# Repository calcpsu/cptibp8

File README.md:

# CalcPack TI BP8

A Li-Po battery replacement design for TI BP7/8/9 battery pack calculators - e.g. TI-55, TI-30, TI Programmer, etc. The original batteries had ~ 500mAh capacity (@2.4V: 1.2Wh), while a typical 9V alkaline battery substitution as ~500mAh (@9V: 4.5Wh), albeit single-use only.

Li-Po has the advantage of far reduced self-discharge in comparison to Ni-Cd, which is an advantage for an intermittently-used device. Even with similar mAh capacity, we can expect longer battery life.

Ni-CD batteries are notorious for leaking. While Lithium Ion batteries are notorious for self-immolation, a well protected Li-Po battery (particularly in a low current application like this) should be able to be made very safe.

## Features / design goals:
- Direct replacement for a BP8 battery pack, compatible with TI55, TI30, TI Programmer (and other Majestic series).
    - Support both 9V battery snap terminal and 3-pin molex connector output
- Compatible with existing charging connection (2-pin AC input; somewhere from 5 to 9VAC)
    - Provides adequate smoothing of rectified AC
    - Provides voltage clamping / overvoltage protection
- Efficient conversion of input rectified supply to 5VDC for charging IC and calculator operation
- Step up from battery or input rectified supply to 9VDC for calculator supply
- Protected from:
    - Overvoltage (input) at 2x rated voltage and current (IATA requirement)
    - Overcharging (4.2V)
    - Over-discharge (3.1V shutdown, 2.5V cutoff in battery pack)
    - Short circuit and overcurrent (again for IATA requirement)
- Minimum idle/quiescent current to maximise charge time
- Similar or higher capacity than typical Ni-MH altenative (1500mAh @ 2.4V: 3.6Wh)

## Case ##

The board is designed to fit into the original TI case bottom part, to preserve an original look!

1. The simplest installation is to place the board and 3D printed standoff into the original case bottom, with a dab of hot glue to hold it in place.
    * The original back cover will not fit, due to ridges for cylindrical cells - you can leave it off.
    * If you prefer, a 3d-printed replacement top cover is provided compatible with the original bottom part. Due to tolerances and thin snaps, SLA 3D printing is recommended (and use a semi-flexible material, such as ABS-like resin).
3. If you don't have an original case, a case designed specifically for 3D printing is available (image below).
    * Files with and without support (intended for SLA printing) are provided.
    * The top part is not required. It is designed to be attached with a couple of dots of superglue.

## Availability ##

If you'd like one of these, I may be able to help! Please contact me at info@calcpsu.com.au.
  
## License

This work is licensed under a
[Creative Commons Attribution-NonCommercial-ShareAlike 4.0 International License][cc-by-nc-sa].

[![CC BY-NC-SA 4.0][cc-by-nc-sa-image]][cc-by-nc-sa]

[cc-by-nc-sa]: http://creativecommons.org/licenses/by-nc-sa/4.0/
[cc-by-nc-sa-image]: https://licensebuttons.net/l/by-nc-sa/4.0/88x31.png
[cc-by-nc-sa-shield]: https://img.shields.io/badge/License-CC%20BY--NC--SA%204.0-lightgrey.svg

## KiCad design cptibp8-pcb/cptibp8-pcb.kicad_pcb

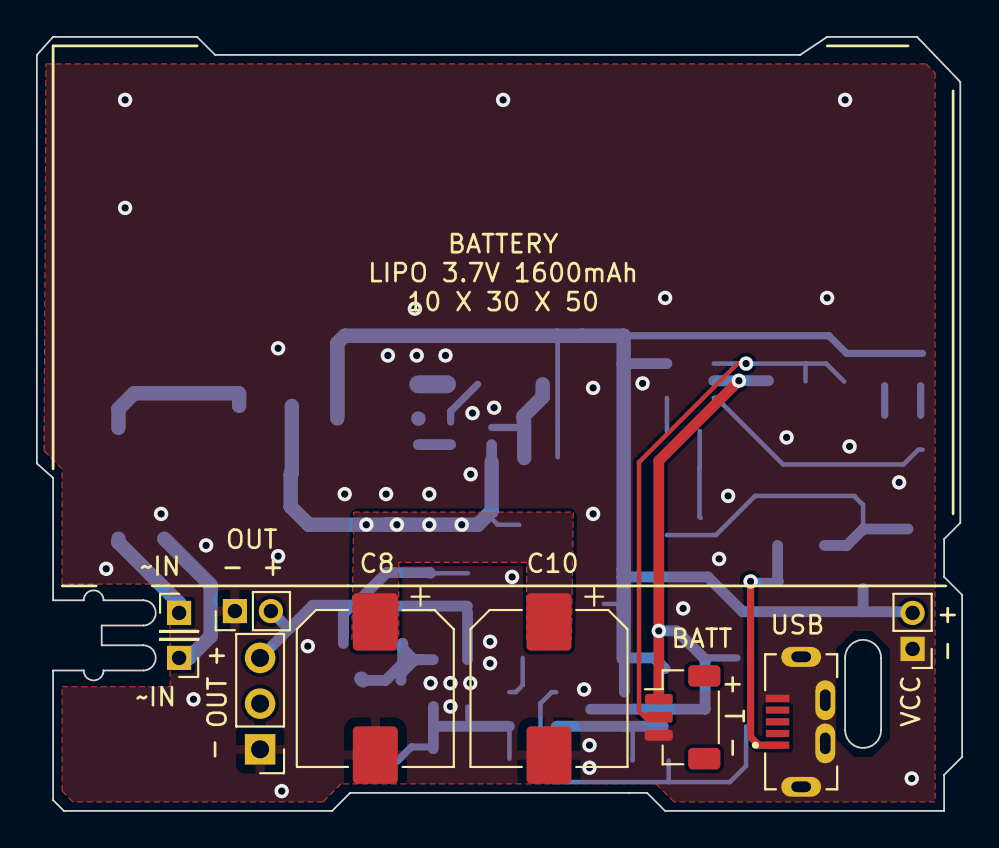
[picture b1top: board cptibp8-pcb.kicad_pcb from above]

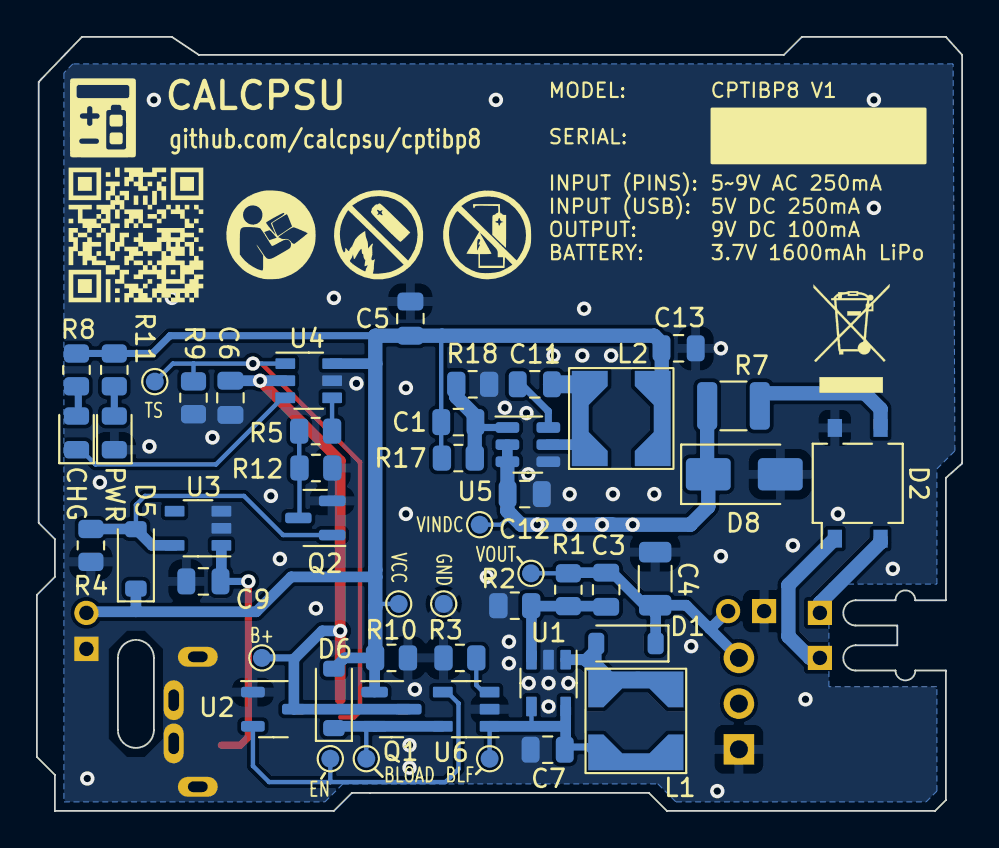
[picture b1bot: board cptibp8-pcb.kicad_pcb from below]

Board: 2 copper layers, 51.4 x 43.0 mm, 58 parts (49 on the bottom side), 25 nets.

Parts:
BT1: LiPo; JST_SH_BM03B-SRSS-TB_1x03-1MP_P1.00mm_Vertical
C1: 100p; C_0805_2012Metric
C3: N/P; C_0805_2012Metric
C4: 22u; C_1206_3216Metric
C5: 10u; C_0805_2012Metric
C6, C7: 4u7; C_0805_2012Metric
C8, C10: 470u/25V; CP_Elec_8x10.5
C9, C12, C13: 1u; C_0805_2012Metric
C11: 22n; C_0805_2012Metric
D1, D5, D6: PMEG40T10ERX; D_SOD-123
D2: MB14S; TO-269AA
D3: RED; LED_0805_2012Metric
D4: GRN; LED_0805_2012Metric
D8: Z15V; D_SMA
J1: VAC2; PinHeader_1x01_P2.00mm_Vertical
J2: OUT; PinHeader_1x02_P2.00mm_Vertical
J3: VCC; PinHeader_1x02_P2.00mm_Vertical
J4: OUT; PinHeader_1x03_P2.54mm_Vertical
J5: VAC1; PinHeader_1x01_P2.00mm_Vertical
J7: ZX80-B-5P_30_; HRS_ZX80-B-5P_30_
L1, L2: 10uH; Inductor_Bourns_SRR4028
Q1: AO3413; SOT-23
Q2: 2N7002; SOT-23
R1: 100k; R_0805_2012Metric
R2: 16k; R_0805_2012Metric
R3, R4, R9: 10k; R_0805_2012Metric
R5: 1k8; R_0805_2012Metric
R7: 1; R_1210_3225Metric
R8, R11: 3k; R_0805_2012Metric
R10: 47k; R_0805_2012Metric
R12: 3k6; R_0805_2012Metric
R17: 49.9k; R_0805_2012Metric
R18: 9.1k; R_0805_2012Metric
TP1: VINDC; TestPoint_Pad_D1.0mm
TP2: B+; TestPoint_Pad_D1.0mm
TP3: BLOAD; TestPoint_Pad_D1.0mm
TP4: VOUT; TestPoint_Pad_D1.0mm
TP5: BLOADF; TestPoint_Pad_D1.0mm
TP6: GND; TestPoint_Pad_D1.0mm
TP7: EN; TestPoint_Pad_D1.0mm
TP8: TS; TestPoint_Pad_D1.0mm
TP9: VCC; TestPoint_Pad_D1.0mm
U1: MIC2250-1YD5-TR; SOT-23-5_TI_DBV5
U2: APX809S-31SA; SOT-23-3
U3: NCP360SNT; SOT-23-5_TI_DBV5
U4: BQ21040; SOT-23-6_TI_DBV6
U5: AP63200WU; TSOT-23-6
U6: NCP380; SOT-23-5_TI_DBV5

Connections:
/B+: BT1.1, C6.1, Q1.3 (D), TP2.1, U2.3 (VCC), U4.2 (VOUT)
/BLOAD: D6.1 (K), Q1.2 (S), TP3.1, U6.5 (IN)
/BLOADF: C7.1, L1.1, TP5.1, U1.4 (EN), U1.5 (VIN), U6.1 (OUT)
/CHG: D3.1 (K), U4.3 (~CHG)
/EN: TP7.1, U2.2 (~RESET), U6.4 (EN)
/GND: BT1.3, C4.2, C5.2, C6.2, C7.2, C8.2, C9.2, C10.2, C12.2, C13.2, D2.4 (-), D4.1 (K), D8.2 (A), J2.1, J3.1, J4.1, J7.5 (GND), J7.SH1 (SHIELD), J7.SH2 (SHIELD__1), J7.SH3 (SHIELD__2), J7.SH4 (SHIELD__3), Q2.2 (S), R2.1, R3.1, R4.1, R9.1, R10.1, R12.1, R18.2, TP6.1, U1.2 (GND), U2.1 (GND), U3.2 (GND), U3.3 (~EN), U4.5 (GND), U5.4 (GND), U6.2 (GND)
/LCHG: D3.2 (A), R8.1
/LPWR: D4.2 (A), R11.1
/PROG: R5.2, U4.4 (ISET)
/PROG2: Q2.3 (D), R5.1, R12.2
/REG5_BS: C11.1, U5.6 (BST)
/REG5_FB: C1.1, R17.2, R18.1, U5.1 (FB)
/REG5_SW: C11.2, L2.1, U5.5 (SW)
/RFB: C3.1, R1.2, R2.2, U1.3 (FB)
/RSW: D1.2 (A), L1.2, U1.1 (SW)
/TS: BT1.2, R9.2, TP8.1, U4.1 (TS)
/VAC1: D2.2, J5.1
/VAC2: D2.1, J1.1
/VBUS: D5.2 (A), Q2.1 (G), R4.2, U3.5 (OUT)
/VBUS1: C9.1, J7.1 (VBUS), U3.1 (IN)
/VCC: C1.2, C5.1, C13.1, D5.1 (K), D6.2 (A), J3.2, L2.2, Q1.1 (G), R8.2, R10.2, R11.2, R17.1, TP9.1, U4.6 (VIN)
/VINDC: C8.1, C10.1, C12.1, D8.1 (K), R7.2, TP1.1, U5.2 (EN), U5.3 (IN)
/VOUT: C3.2, C4.1, D1.1 (K), J2.2, J4.3, R1.1, TP4.1
/VRECT: D2.3 (+), R7.1
unnamed: R3.2, U6.3 (~FLG)

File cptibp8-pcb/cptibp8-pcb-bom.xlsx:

Id | Designator | Footprint | Quantity | Designation | Supplier and ref | Column1 | _1 | MPN
6 | BT1 | JST_SH_BM03B-SRSS-TB_1x03-1MP_P1.00mm_Vertical | 1 | LiPo |  |  |  | BM03B-SRSS-TB
25 | C1 | C_0805_2012Metric | 1 | 100p |  |  |  | CC0805KRX7R8BB101
12 | C11 | C_0805_2012Metric | 1 | 22n |  |  |  | CC0805KRX7R8BB223
14 | C13,C12,C2 | C_0805_2012Metric | 3 | 1u |  |  |  | CL21B105KAFNNNE
18 | C3 | C_0805_2012Metric | 1 | 1n |  |  |  | CL21C472JAFNNNE
43 | C4 | C_1206_3216Metric | 1 | 22u |  |  |  | CL31A226KAHNNNE
41 | C5 | C_0805_2012Metric | 1 | 10u |  |  |  | CL21A106KAYNNNE
46 | C7,C6 | C_0805_2012Metric | 2 | 4u7 |  |  |  | CL21A475KAQNNNE
3 | C8,C10 | CP_Elec_8x10.5 | 2 | 470u/25V |  |  |  | EEE-FP1C471AP
34 | D1,D6 | D_SOD-123 | 2 | PMEG40T10ERX |  |  |  | PMEG40T10ERX_x000D_
17 | D2 | TO-269AA | 1 | MB14S |  |  |  | MB14S
28 | D3 | LED_0805_2012Metric | 1 | RED |  |  |  | B1701USD-20D000114U1930
35 | D4 | LED_0805_2012Metric | 1 | GRN |  |  |  | B1701UYG-20D000114U1930
36 | D8 | D_SMA | 1 | Z15V |  |  |  | 3SMAJ5929B-TP
45 | F1 | Fuse_1210_3225Metric | 1 | 0ZCJ0035AF2E |  |  |  | 0ZCJ0035AF2E
1 | J1 | PinHeader_1x01_P2.00mm_Vertical | 1 | VAC2 |  |  |  | #N/A
2 | J2 | PinHeader_1x02_P2.00mm_Vertical | 1 | OUT |  |  |  | 232
7 | J3 | PinHeader_1x02_P2.00mm_Vertical | 1 | VCC |  |  |  | #N/A
4 | J4 | PinHeader_1x03_P2.54mm_Vertical | 1 | OUT |  |  |  | 22052031
5 | J5 | PinHeader_1x01_P2.00mm_Vertical | 1 | VAC1 |  |  |  | #N/A
31 | L2,L1 | Inductor_Bourns_SRR4028 | 2 | 10uH |  |  |  | SRR4028-100Y
24 | Q1 | SOT-23 | 1 | AO3413 |  |  |  | AO3413
19 | Q3 | SOT-23 | 1 | DMG2302UK |  |  |  | DMG2302U-7
23 | R1 | R_0805_2012Metric | 1 | 576k |  |  |  | RC0805FR-07576KL
10 | R10 | R_0805_2012Metric | 1 | 47k |  |  |  | RC0805FR-0747KL
11 | R11,R8 | R_0805_2012Metric | 2 | 3k |  |  |  | RC0805FR-073KL
29 | R14 | R_0805_2012Metric | 1 | 5k4 |  |  |  | RC0805FR-071K3L
16 | R17 | R_0805_2012Metric | 1 | 49.9k |  |  |  | RC0805FR-0749K9L
42 | R18 | R_0805_2012Metric | 1 | 9.1k |  |  |  | RC0805FR-079K1L
44 | R2 | R_0805_2012Metric | 1 | 91k |  |  |  | RC0805FR-0791KL
21 | R6 | R_0805_2012Metric | 1 | 1M |  |  |  | RC0805FR-7W1ML
30 | R7 | R_1210_3225Metric | 1 | 1 |  |  |  | RC1210FR-071RL
15 | R9 | R_0805_2012Metric | 1 | 10k |  |  |  | RC0805FR-0710KL
22 | TP1 | TestPoint_Pad_D1.0mm | 1 | VINDC |  |  |  | #N/A
26 | TP10 | TestPoint_Pad_D1.0mm | 1 | VOUTN |  |  |  | #N/A
13 | TP2 | TestPoint_Pad_D1.0mm | 1 | B+ |  |  |  | #N/A
33 | TP3 | TestPoint_Pad_D1.0mm | 1 | BLOAD |  |  |  | #N/A
40 | TP4 | TestPoint_Pad_D1.0mm | 1 | VOUT |  |  |  | #N/A
48 | TP5 | TestPoint_Pad_D1.0mm | 1 | VOUTF |  |  |  | #N/A
38 | TP6 | TestPoint_Pad_D1.0mm | 1 | GND |  |  |  | #N/A
47 | TP7 | TestPoint_Pad_D1.0mm | 1 | EN |  |  |  | #N/A
20 | TP8 | TestPoint_Pad_D1.0mm | 1 | TS |  |  |  | #N/A
39 | TP9 | TestPoint_Pad_D1.0mm | 1 | VCC |  |  |  | #N/A
37 | U1 | SOT-23-5_TI_DBV5 | 1 | MIC2250-1YD5-TR |  |  |  | MIC2250-1YD5-TR
9 | U2 | SOT-23-3 | 1 | APX803S-31SA |  |  |  | APX803S-31SA
32 | U4 | SOT-23-6_TI_DBV6 | 1 | BQ21040 |  |  |  | BQ21040DBVR
27 | U5 | TSOT-23-6 | 1 | AP63200WU |  |  |  | AP63200WU-7

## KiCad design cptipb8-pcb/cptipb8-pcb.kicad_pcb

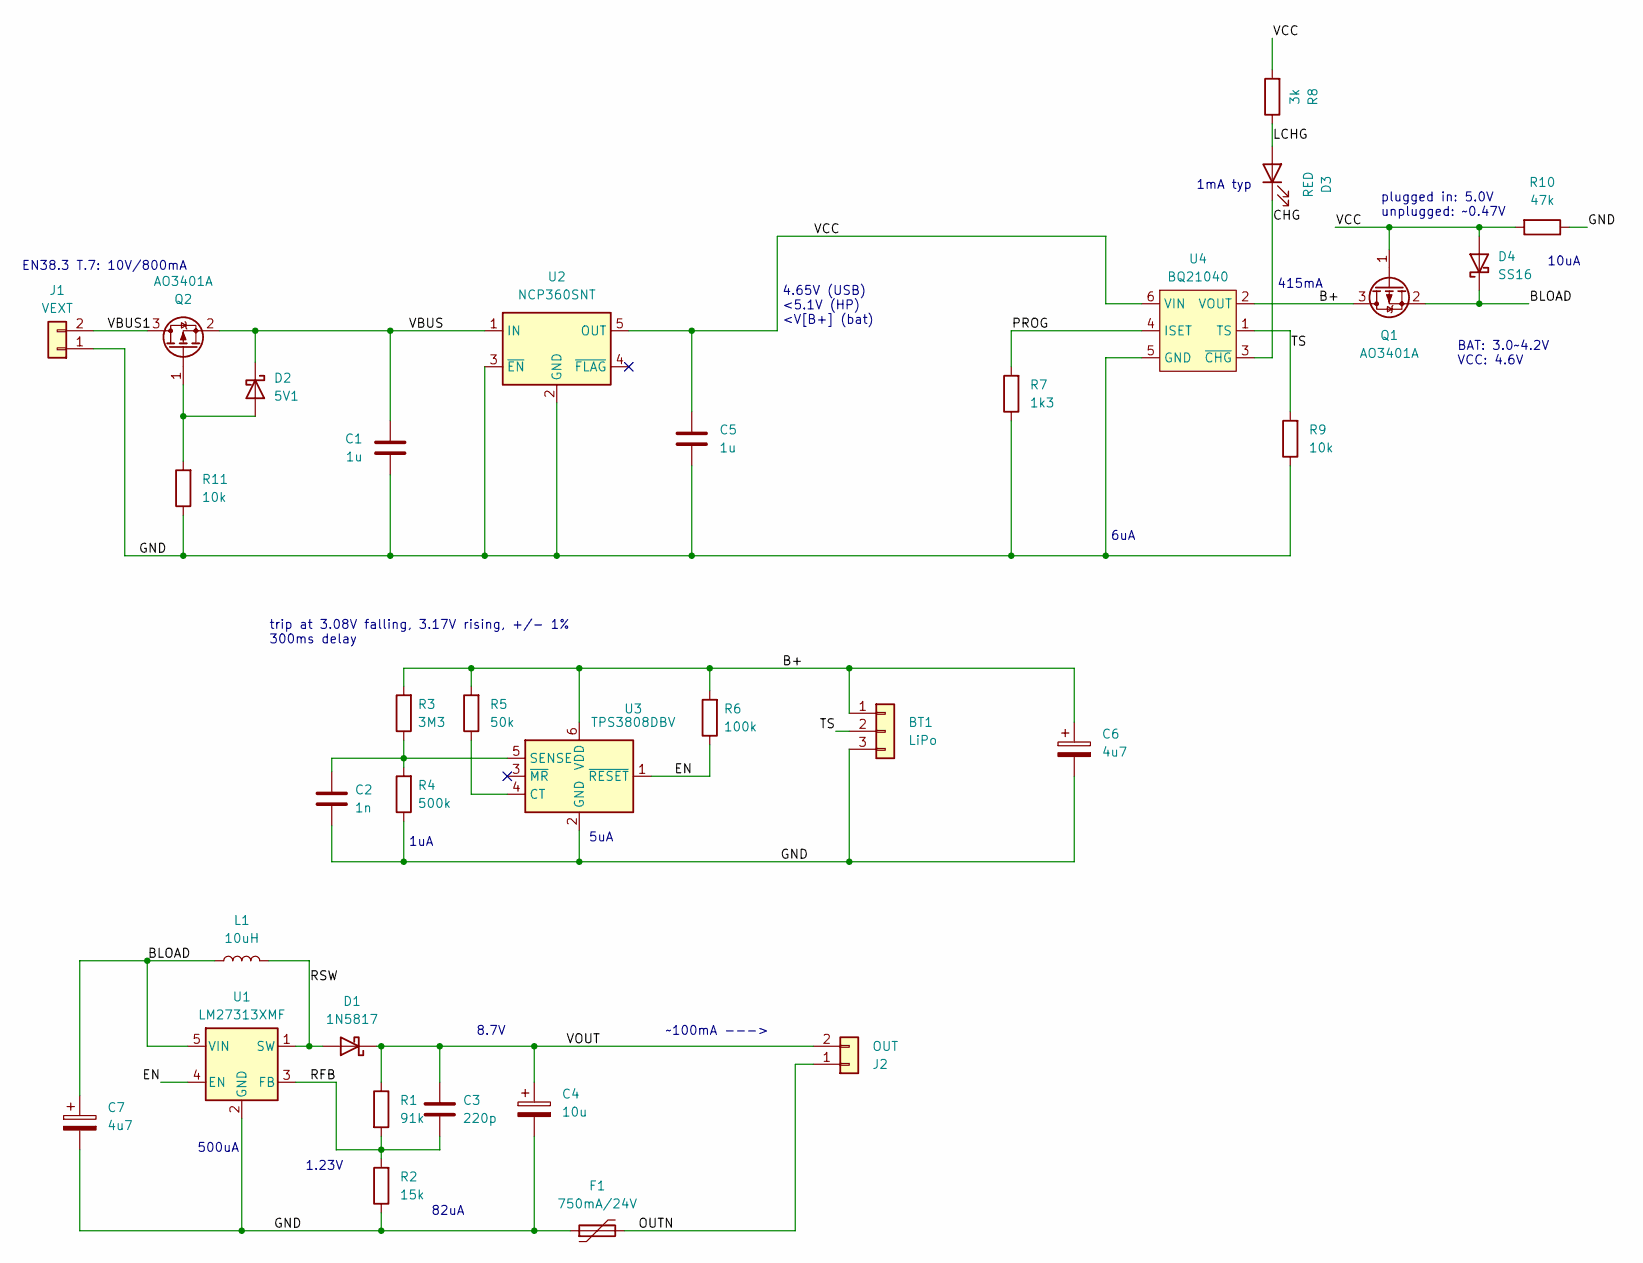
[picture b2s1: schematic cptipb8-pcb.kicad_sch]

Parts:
BT1: LiPo; JST_SH_BM03B-SRSS-TB_1x03-1MP_P1.00mm_Vertical
C1, C5: 1u; C_0805_2012Metric
C2: 1n; C_0805_2012Metric
C3: 220p; C_0805_2012Metric
C4: 10u; C_1206_3216Metric
C6, C7: 4u7; C_0805_2012Metric
D1: 1N5817; D_SOD-123
D2: 5V1; D_SOD-123
D3: RED; LED_0805_2012Metric
D4: SS16; D_SOD-123
F1: 750mA/24V; Fuse_1210_3225Metric
J1: VEXT; PinHeader_1x02_P2.54mm_Horizontal
J2: OUT; PinHeader_1x02_P2.00mm_Vertical
L1: 10uH; Inductor_Bourns_SRR4028
Q1, Q2: AO3401A; SOT-23
R1: 91k; R_0805_2012Metric
R2: 15k; R_0805_2012Metric
R3: 3M3; R_0805_2012Metric
R4: 500k; R_0805_2012Metric
R5: 50k; R_0805_2012Metric
R6: 100k; R_0805_2012Metric
R7: 1k3; R_0805_2012Metric
R8: 3k; R_0805_2012Metric
R9, R11: 10k; R_0805_2012Metric
R10: 47k; R_0805_2012Metric
U1: LM27313XMF; SOT-23-5_TI_DBV5
U2: NCP360SNT; SOT-23-5_TI_DBV5
U3: TPS3808DBV; SOT-23-6_TI_DBV6
U4: BQ21040; SOT-23-6_TI_DBV6

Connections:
/B+: BT1.1, C6.1, Q1.3 (D), R3.2, R5.2, R6.2, U3.6 (VDD), U4.2 (VOUT)
/BLOAD: C7.1, D4.1 (K), L1.1, Q1.2 (S), U1.5 (VIN)
/CHG: D3.1 (K), U4.3 (~CHG)
/EN: R6.1, U1.4 (EN), U3.1 (~RESET)
/GND: BT1.3, C1.2, C2.2, C4.2, C5.2, C6.2, C7.2, F1.1, J1.1, R2.1, R4.1, R7.1, R9.1, R10.1, R11.1, U1.2 (GND), U2.2 (GND), U2.3 (~EN), U3.2 (GND), U4.5 (GND)
/LCHG: D3.2 (A), R8.1
/OUTN: F1.2, J2.1
/PROG: R7.2, U4.4 (ISET)
/RFB: C3.1, R1.2, R2.2, U1.3 (FB)
/RSW: D1.2 (A), L1.2, U1.1 (SW)
/TS: BT1.2, R9.2, U4.1 (TS)
/VBUS: C1.1, D2.1 (K), Q2.2 (S), U2.1 (IN)
/VBUS1: J1.2, Q2.3 (D)
/VCC: C5.1, D4.2 (A), Q1.1 (G), R8.2, R10.2, U2.5 (OUT), U4.6 (VIN)
/VOUT: C3.2, C4.1, D1.1 (K), J2.2, R1.1
unnamed: D2.2 (A), Q2.1 (G), R11.2
unnamed: R5.1, U3.4 (CT)
unnamed: C2.1, R3.1, R4.2, U3.5 (SENSE)

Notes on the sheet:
~100mA --->
500uA
4.65V (USB) <5.1V (HP) <V[B+] (bat)
8.7V
BAT: 3.0~4.2V VCC: 4.6V
1.23V
EN38.3 T.7: 10V/800mA
415mA
1uA
trip at 3.08V falling, 3.17V rising, +/- 1% 300ms delay
5uA
10uA
1mA typ
6uA
82uA
plugged in: 5.0V unplugged: ~0.47V

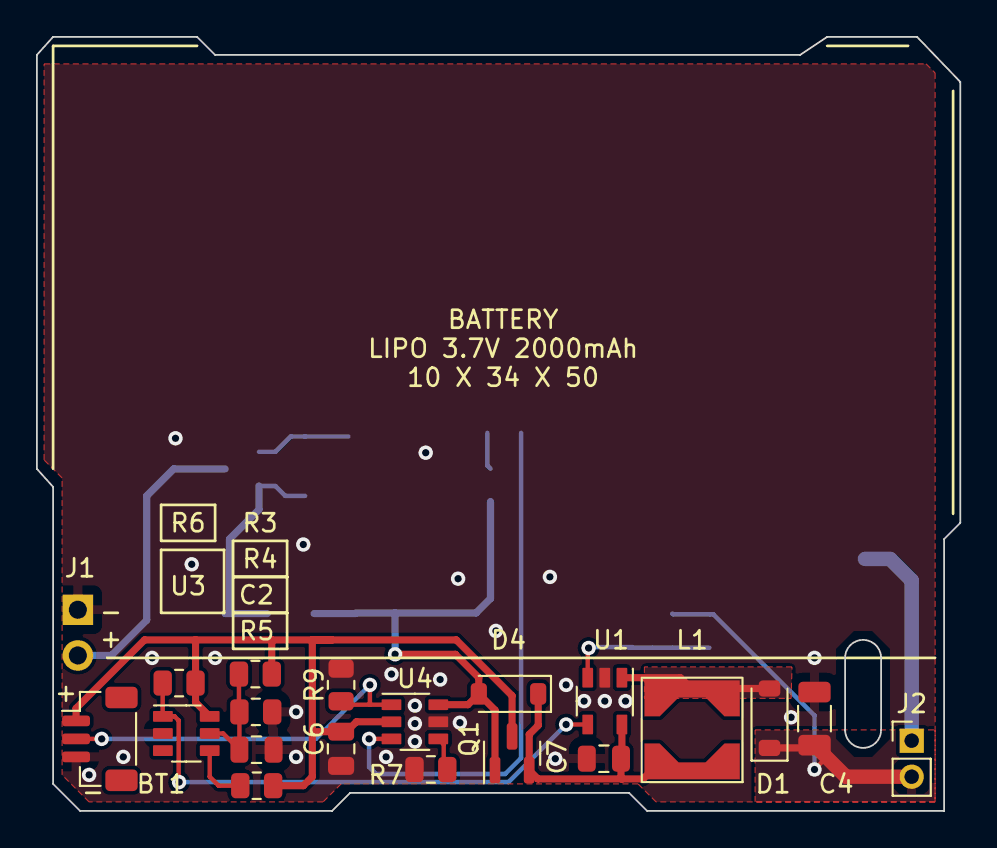
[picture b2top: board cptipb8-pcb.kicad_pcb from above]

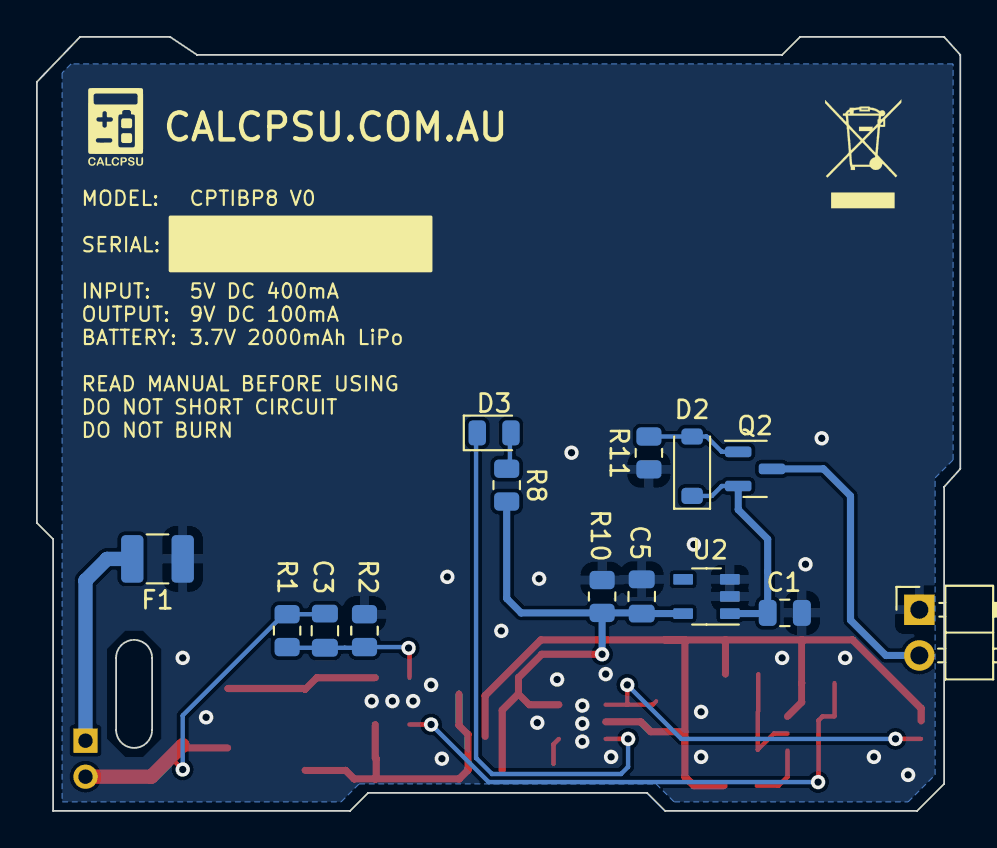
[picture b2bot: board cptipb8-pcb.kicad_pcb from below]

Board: 2 copper layers, 51.3 x 43.0 mm, 34 parts (15 on the bottom side), 18 nets.

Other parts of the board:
REFe: graphic_calcpsulogo

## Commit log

2024-01-10 Create LICENSE
2024-01-10 initial commit for pcb
2024-01-17 Fix typo. Update design.
2024-01-18 move sim
2024-01-18 docs
2024-01-22 rev0.3
2024-01-29 rev0 final
2024-01-29 added sim
2024-03-06 update enclosure and project
2024-04-24 rev1
2024-09-24 Update/move render
2024-09-24 Update kicad file version (8.0)
2024-09-24 Add case
2024-09-25 Minor tweaks to case design
